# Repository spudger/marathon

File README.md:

# Marathon

A handheld retro gaming console built around a Raspberry Pi Zero 2 W, designed for long battery life through a custom PCB that places every power, audio, and amplifier IC as a bare chip directly on the board.

## Status

- 🔨 **Phase 1, Component identification & research:** mostly complete.
- ✅ **Phase 2, Breadboard prototype:** complete. All subsystems (power, display, audio, buttons) verified end-to-end on 2026-04-03 / 2026-04-04.
- 🔨 **Phase 3, Schematic capture (KiCad):** mostly complete. ERC is clean; a readability pass on the sheet remains.
- 🔨 **Phase 4, PCB layout (KiCad):** in progress. Placement and routing are done, and DRC reports 0 errors. Provisional footprints still need checking against the real parts, and there are no fabrication files yet. Not ready for fabrication.
- 🔨 **Phase 5, Case design:** first concept modeled in CadQuery, with STLs and renders in [`case/`](case/). Not printed yet, and several part sizes are provisional.

See the [Phases](#phases) table below for the full roadmap.

## Design

Marathon integrates its power management (BQ25616 charger, TPS61023 boost, LTC2954 power key controller and MAX17048 fuel gauge), I²S DAC (PCM5102A), and class-D amplifier (PAM8403) as bare ICs on a single custom PCB. The final board is planned for SMT assembly via JLCPCB. The design dedicates internal case volume to a thin, high-capacity LiPo cell, the source of the "Marathon" name.

Design highlights:

- **Bare-chip build.** Every IC is soldered directly to the PCB, not mounted on breakout modules.
- **Safe charging and clean shutdown.** A BQ25616 charges the cell at 0.9 A, only between 0 °C and 45 °C, and runs the device from USB while it charges. A TPS61023 boosts the cell to 5 V. The power key turns the device on with a 1 s hold and shuts Linux down cleanly with a short press; a MAX17048 gauge reports the battery level so the Pi can shut down before the cell runs out.
- **Long-life battery.** Target about 4000 mAh, from a 105060-class cell about 10 mm thick. The board reserves a 67 x 59 mm area on the back, for a cell up to 57 x 65 mm with its protection board (`planning/specs/022-BATTERY-SPACE.md`).
- **Direct I²S audio chain.** Pi → PCM5102A DAC → PAM8403 amplifier → two speakers. A hardware SPDT mute switch holds the amp in shutdown for instant silence, and fixed attenuation keeps full-scale audio under the speakers' 1 W rating at the amp's nominal gain. Fine volume control is handled in RetroPie.
- **Direct GPIO input.** Silicone membrane pads for the D-pad and ABXY, tactile switches for Start, Select, and shoulder buttons. No I²C expander.
- **USB-C with spec-compliant CC resistors.** Works with any USB-C cable, not just A-to-C.
- **Landscape handheld form factor.** A 160 x 75 mm board with the screen in the middle, the D-pad on the left, and the face buttons on the right.

The main board without its case, front and back, rendered from the KiCad layout.

## System Architecture

Power flow and signal flow across the Marathon hardware:

```mermaid
flowchart LR
    USBC[USB-C in]
    BAT[3.7V LiPo<br/>about 4000 mAh]
    CHG[BQ25616<br/>charger + power path]
    BOOST[TPS61023<br/>5V boost]
    KEY[LTC2954<br/>power key]
    GAUGE[MAX17048<br/>fuel gauge]
    V5((5V rail))
    V33((3.3V rail))
    PI[Raspberry Pi<br/>Zero 2 W]
    MUTE{SPDT mute<br/>switch}
    PAM[PAM8403<br/>class-D amp]
    DAC[PCM5102A<br/>I2S DAC]
    LCD[ILI9341<br/>3.2 inch SPI LCD]
    SPK1[Speaker L]
    SPK2[Speaker R]
    DPAD[D-pad<br/>silicone pad]
    ABXY[ABXY<br/>silicone pad]
    TACT[Start / Select<br/>L / R shoulders]

    USBC --> CHG
    BAT <--> CHG
    CHG -->|SYS| BOOST
    BOOST --> V5
    KEY -->|enable| BOOST
    KEY <-->|shutdown request / kill| PI
    BAT --- GAUGE
    GAUGE -->|I2C| PI
    V5 --> PI
    V5 --> PAM
    MUTE -->|shutdown| PAM
    V5 -->|backlight| LCD
    PI --> V33
    V33 --> LCD
    V33 --> DAC
    PI -->|SPI| LCD
    PI -->|I2S| DAC
    DAC -->|analog L/R| PAM
    PAM --> SPK1
    PAM --> SPK2
    DPAD -->|GPIO| PI
    ABXY -->|GPIO| PI
    TACT -->|GPIO| PI
```

## Phases

| Phase | Scope | Status |
|-------|-------|--------|
| 1 | Component identification & research | 🔨 Mostly complete |
| 2 | Breadboard prototype | ✅ Complete (2026-04-03 / 2026-04-04) |
| 3 | Schematic capture (KiCad) | 🔨 Mostly complete |
| 4 | PCB layout (KiCad) | 🔨 In progress |
| 5 | Case design (3D print) | 🔨 First concept |
| 6 | Software & RetroPie tuning | 🔨 Partial (validated during Phase 2) |
| 7 | Fabrication & final assembly (JLCPCB + hand-solder) | ⏳ Planned |

Full phase detail is in [`documentation/PROJECT_PLAN.md`](documentation/PROJECT_PLAN.md).

## Repository Layout

```
marathon/
├── .claude/skills/verify-marathon/       ERC, DRC, BOM and renders of the KiCad project, vs main
├── README.md                             this file
├── LICENSE                               CERN-OHL-P v2
├── bom/                                  bill of materials, sourcing, decision log
├── documentation/
│   ├── PROJECT_PLAN.md                   design overview, architecture, phase roadmap
│   ├── PIN_MAPPING.md                    complete 40-pin GPIO map across all subsystems
│   └── PROTOTYPE_BUILD_GUIDE.md          step-by-step breadboard prototype build guide
├── schematics/                           schematic PDF export (planned)
├── pcb/                                  KiCad 10 project: schematic, layout, libraries, renders
├── case/                                 the 3D-printed case: CadQuery source, STEP, STLs, renders
├── software/                             firmware and OS configuration (Phase 6)
└── tools/render/                         board renders and the stand-in 3D models
```

`software/` is a placeholder for a later phase.

## Build Documentation

- **Breadboard prototype build:** [`documentation/PROTOTYPE_BUILD_GUIDE.md`](documentation/PROTOTYPE_BUILD_GUIDE.md): full walkthrough from USB-C cable harvest through verified I²S audio and joystick input, including all config files and gotchas.
- **Pin mapping:** [`documentation/PIN_MAPPING.md`](documentation/PIN_MAPPING.md): the full 40-pin GPIO table, subsystem breakdowns, and display / audio / button pin assignments.
- **Bill of materials:** [`bom/`](bom/): every component with specs, costs, sourcing, and a running decision log.
- **Project plan:** [`documentation/PROJECT_PLAN.md`](documentation/PROJECT_PLAN.md): architecture overview and the full phase roadmap.

## Hardware Stack

| Subsystem | Component | Notes |
|-----------|-----------|-------|
| Compute | Raspberry Pi Zero 2 W | Mounts on the back of the PCB on standoffs, joined by long-tail header pins |
| Display | ILI9341 3.2" SPI LCD | 18-pin FPC ribbon soldered directly to the PCB |
| Audio DAC | PCM5102A (bare IC) | I²S input, line-level output |
| Audio amp | PAM8403 (bare IC) | Class-D stereo, drives two speakers |
| Power | BQ25616, TPS61023, LTC2954, MAX17048 (bare ICs) | Charging with temperature cutoff, 5 V boost, power key with clean shutdown, battery level |
| Battery | 3.7 V LiPo, about 4000 mAh target | 105060-class cell, about 10 mm thick |
| Input | Silicone membrane pads + tactile switches | Direct GPIO, no expander |
| Case | Custom 3D print | First concept: two shells, 164.2 x 79.2 x 18.5 mm, held by four M2 screws (`case/`) |

## License

Licensed under the [CERN Open Hardware Licence version 2, Permissive (CERN-OHL-P v2)](https://ohwr.org/project/cernohl/wikis/Documents/CERN-OHL-version-2). See [`LICENSE`](LICENSE).

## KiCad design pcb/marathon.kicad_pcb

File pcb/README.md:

# PCB

KiCad 10 project for the Marathon main board. Open `marathon.kicad_pro`. The schematic lives here with the layout because KiCad keeps a project's files in one folder.

**Status:** Phase 4, in progress. **Not ready for fabrication.**

- 160 x 75 mm, 2 layers.
- Placed: every part. The Raspberry Pi mounts on the back, inside the outline and clear of the battery area.
- Routed: every net, with ground pours on both layers that fill the rounded corners.
- Four plated M2 case holes (H1 to H4), tied to GND, 5 mm in from each edge.
- 13 test pads (TP1 to TP13) on the back, labeled with their net names, outside the Pi, the microSD card's overhang, the battery and the antenna areas.
- The `PI_ANTENNA_KEEPOUT` rule area keeps tracks, vias, pads and pours off both layers under the Pi Zero 2 W's antenna, plus 5 mm, or 4.2 mm on the left where the D-pad's right contact (SW13) sits. The antenna sits on the Pi's edge opposite the GPIO header, between the mini-HDMI and USB data ports.
- U2 (PCM5102A) and U3 (PAM8403) use their library footprints flipped to the back, so their pin order matches the parts (fixed 2026-11-06). Their capacitors moved with them, and each bypass capacitor sits at the pin the schematic names.
- Footprints named `PROVISIONAL` still need checking against the real parts. The Alps switch footprints follow Alps' published land patterns.
- `marathon.kicad_dru` allows 0.12 mm clearance inside the U5 (SOT-563) and U6 (TSOT-23-8) courtyards, whose stock land patterns put pads 0.15 mm apart.
- The BQ25616 uses a project copy of KiCad's RTW footprint with four 0.3 mm vias in the exposed pad, the board's minimum drill.
- The stackup sets a black solder mask and an ENIG finish on the 1.0 mm board.
- `Marathon.3dshapes/` holds stand-in 3D models for the project footprints, and BT1 is a board-only stand-in for the battery. `tools/render/` builds them and the renders.

## Renders

Flat views: [`renders/top.png`](renders/top.png) and [`renders/bottom.png`](renders/bottom.png). To rebuild them, see [`../tools/render/README.md`](../tools/render/README.md).

## Checks

| Check | Result |
|-------|--------|
| ERC | 0 violations |
| DRC | 0 errors, 0 warnings |
| Unrouted connections | 0 |
| Schematic / PCB parity | 0 issues |

To re-run them from the repo root:

```bash
kicad-cli sch erc pcb/marathon.kicad_sch
kicad-cli pcb drc --refill-zones --schematic-parity pcb/marathon.kicad_pcb
```

## Planned

- A `fab/` folder with Gerbers, drill files, BOM, and pick-and-place files for JLCPCB.

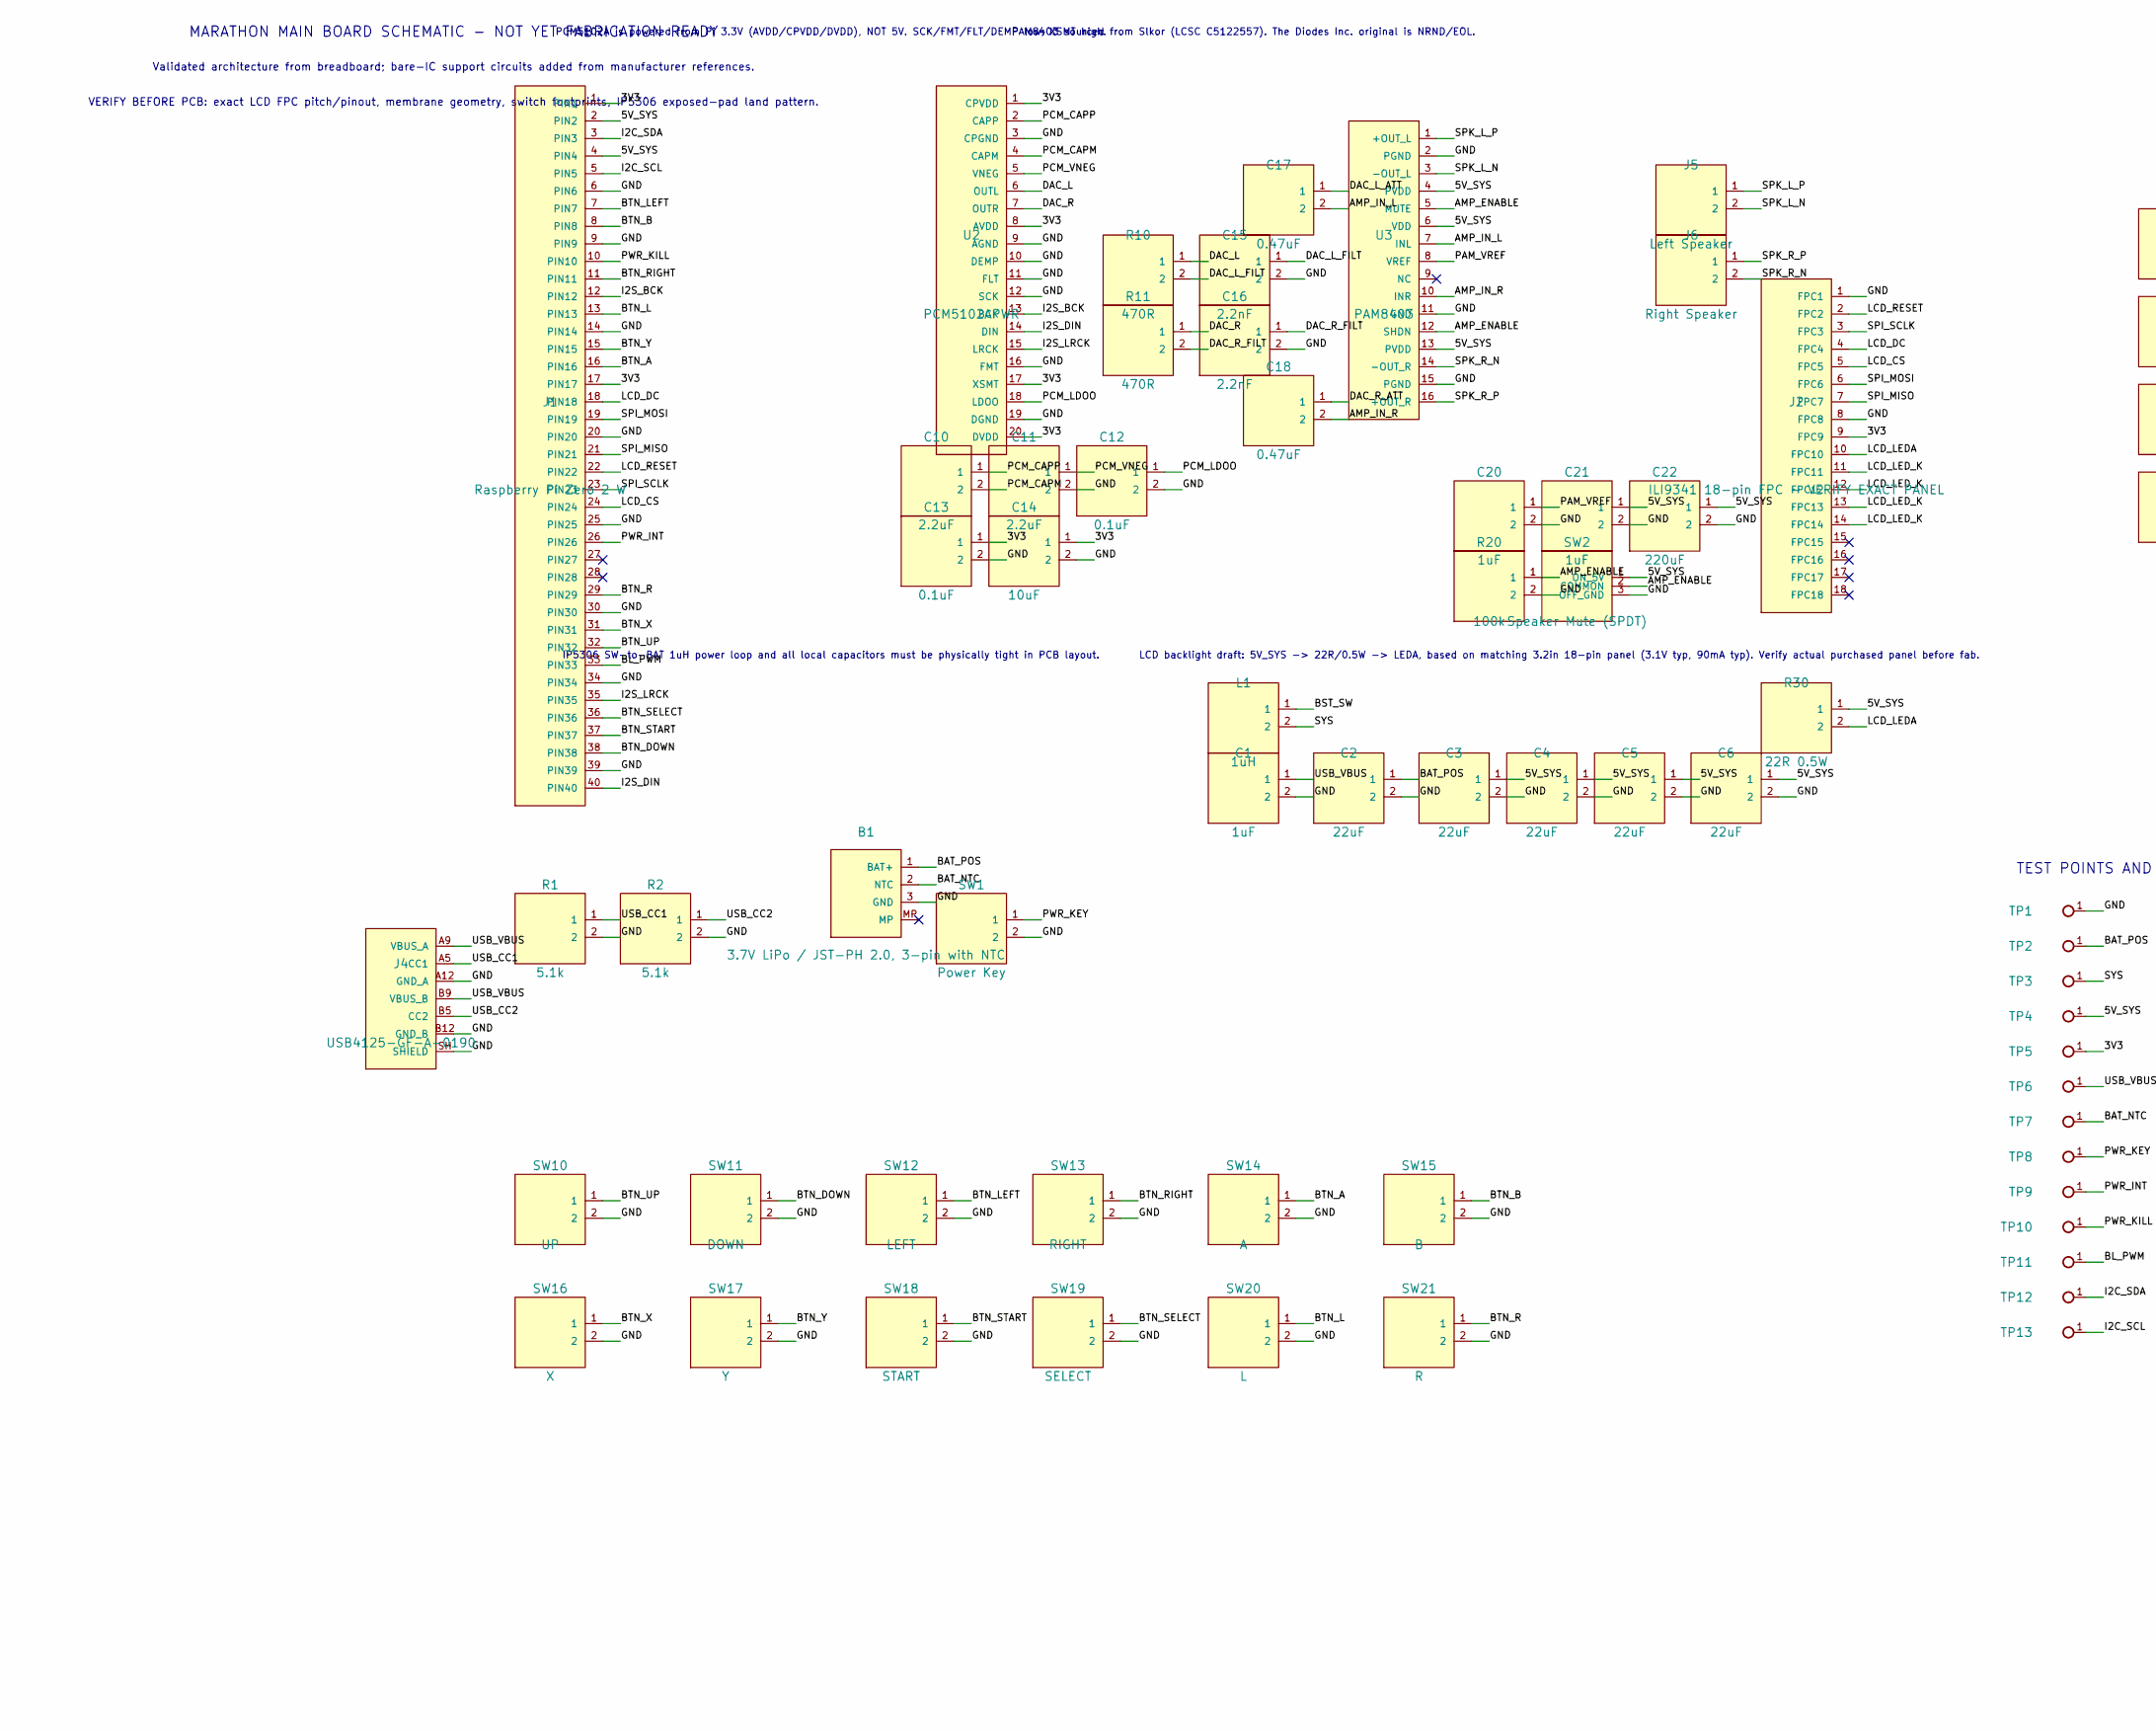
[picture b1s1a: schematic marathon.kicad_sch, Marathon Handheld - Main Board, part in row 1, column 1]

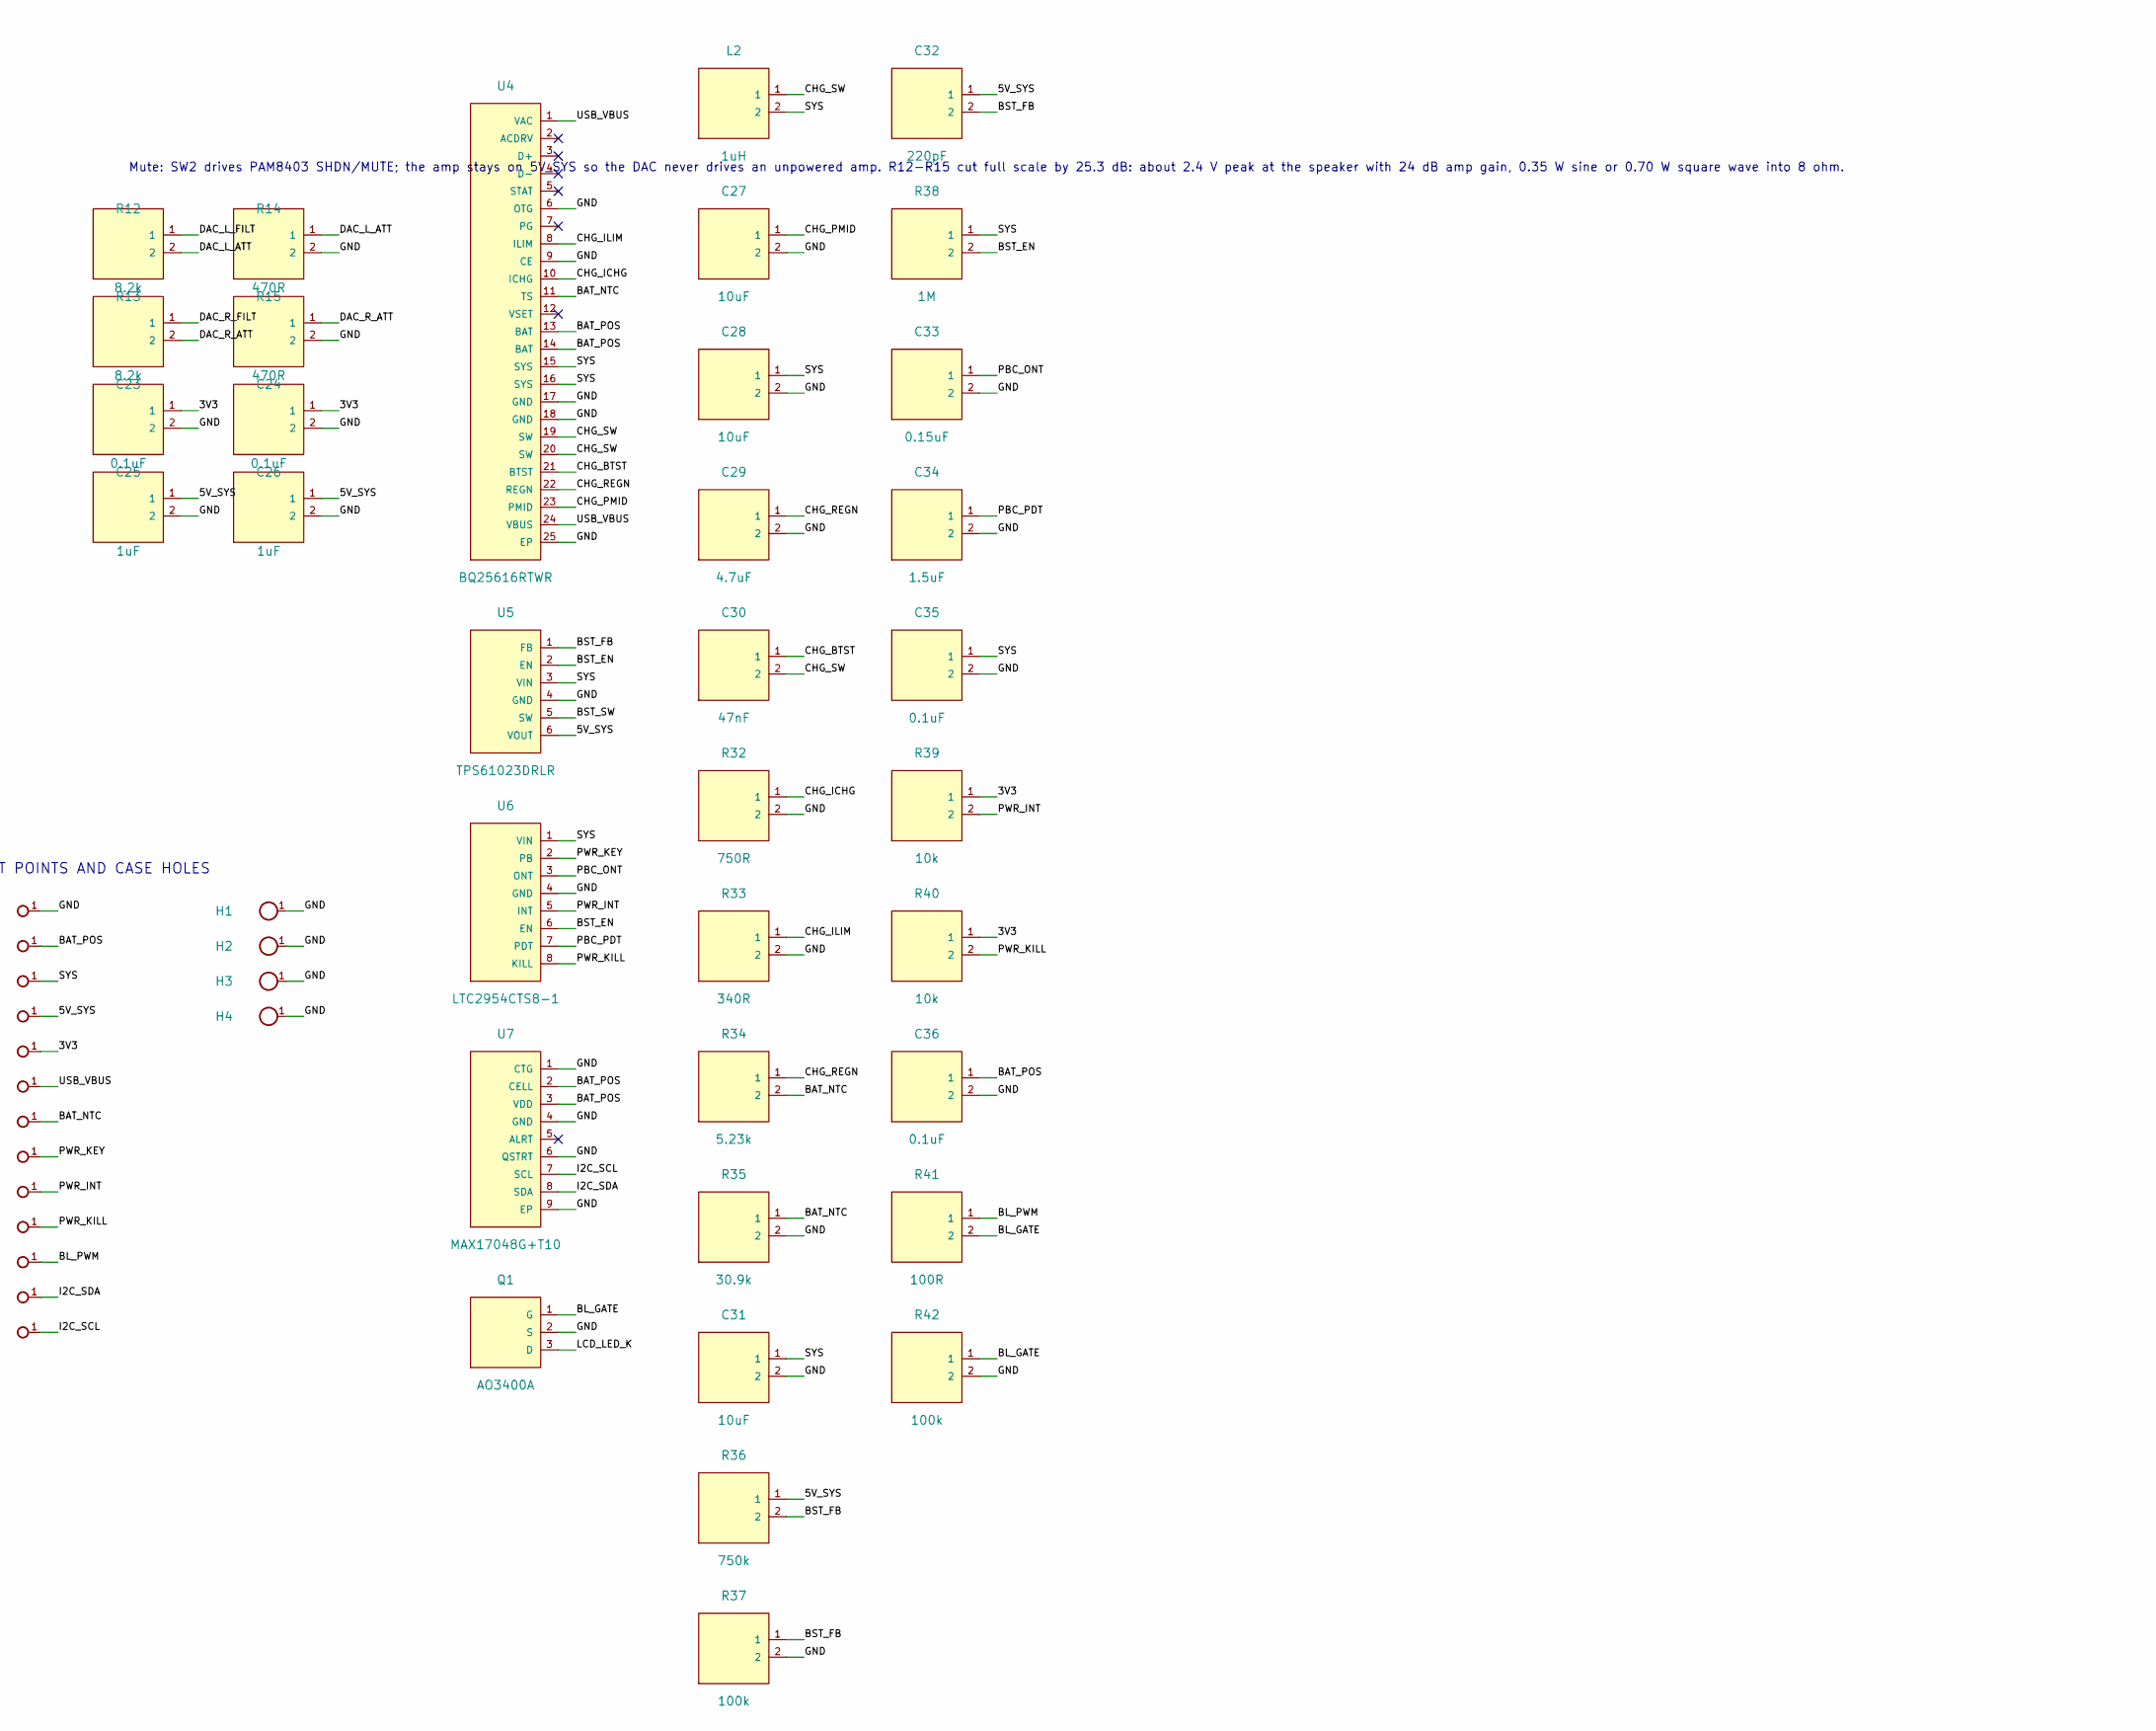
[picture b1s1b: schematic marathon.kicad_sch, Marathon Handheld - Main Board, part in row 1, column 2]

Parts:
B1: 3.7V LiPo / JST-PH 2.0, 3-pin with NTC; JST_PH_S3B-PH-SM4-TB_1x03-1MP_P2.00mm_Horizontal
C1, C21: 1uF; C_0805_2012Metric_Pad1.18x1.45mm_HandSolder
C2, C3, C4, C5, C6: 22uF; C_0805_2012Metric_Pad1.18x1.45mm_HandSolder
C10, C11: 2.2uF; C_0402_1005Metric
C12, C13, C23, C24, C35, C36: 0.1uF; C_0402_1005Metric
C14, C27: 10uF; C_0603_1608Metric
C15, C16: 2.2nF; C_0603_1608Metric
C17, C18: 0.47uF; C_0603_1608Metric
C20, C25, C26: 1uF; C_0603_1608Metric
C22: 220uF; CP_EIA-7343-31_Kemet-D; MPN Panasonic 10TPE220ML; LCSC C147767
C28, C31: 10uF; C_0805_2012Metric_Pad1.18x1.45mm_HandSolder
C29: 4.7uF; C_0603_1608Metric
C30: 47nF; C_0402_1005Metric
C32: 220pF; C_0402_1005Metric
C33: 0.15uF; C_0603_1608Metric; Tolerance 10%
C34: 1.5uF; C_0603_1608Metric; Tolerance 10%
H1, H2, H3, H4: MountingHole_M2; MountingHole_2.2mm_M2_Pad_Via
J1: Raspberry Pi Zero 2 W; Raspberry_Pi_Zero_2W_DirectStack_THT
J2: ILI9341 18-pin FPC - VERIFY EXACT PANEL; LCD_FPC18_P0.8_DirectSolder_PROVISIONAL
J4: USB4125-GF-A-0190; USB_C_Receptacle_GCT_USB4125-xx-x-0190_6P_TopMnt_Horizontal; MPN USB4125-GF-A-0190; LCSC C5246813
J5: Left Speaker; Speaker_WirePads_2P_P5.0
J6: Right Speaker; Speaker_WirePads_2P_P5.0
L1: 1uH; L_Coilcraft_XAL4020-XXX
L2: 1uH; L_1008_2520Metric; MPN TDK TFM252012ALMA1R0MTAA; LCSC C404802
Q1: AO3400A; SOT-23; MPN AO3400A; LCSC C20917
R1, R2: 5.1k; R_0603_1608Metric_Pad0.98x0.95mm_HandSolder
R10, R11, R14, R15: 470R; R_0603_1608Metric_Pad0.98x0.95mm_HandSolder
R12, R13: 8.2k; R_0603_1608Metric_Pad0.98x0.95mm_HandSolder
R20, R42: 100k; R_0603_1608Metric_Pad0.98x0.95mm_HandSolder
R30: 22R 0.5W; R_1206_3216Metric_Pad1.30x1.75mm_HandSolder
R32: 750R; R_0603_1608Metric_Pad0.98x0.95mm_HandSolder; Tolerance 1%
R33: 340R; R_0603_1608Metric_Pad0.98x0.95mm_HandSolder; Tolerance 1%
R34: 5.23k; R_0603_1608Metric_Pad0.98x0.95mm_HandSolder; Tolerance 1%
R35: 30.9k; R_0603_1608Metric_Pad0.98x0.95mm_HandSolder; Tolerance 1%
R36: 750k; R_0603_1608Metric_Pad0.98x0.95mm_HandSolder; Tolerance 1%
R37: 100k; R_0603_1608Metric_Pad0.98x0.95mm_HandSolder; Tolerance 1%
R38: 1M; R_0603_1608Metric_Pad0.98x0.95mm_HandSolder
R39, R40: 10k; R_0603_1608Metric_Pad0.98x0.95mm_HandSolder
R41: 100R; R_0603_1608Metric_Pad0.98x0.95mm_HandSolder
SW1: Power Key; SW_Alps_SKTHACE010_PROVISIONAL; MPN SKTHACE010
SW2: Speaker Mute (SPDT); SS12F15_G5_THT
SW10: UP; Conductive_Pad_5mm_GameBoyStyle
SW11: DOWN; Conductive_Pad_5mm_GameBoyStyle
SW12: LEFT; Conductive_Pad_5mm_GameBoyStyle
SW13: RIGHT; Conductive_Pad_5mm_GameBoyStyle
SW14: A; Conductive_Pad_5mm_GameBoyStyle
SW15: B; Conductive_Pad_5mm_GameBoyStyle
SW16: X; Conductive_Pad_5mm_GameBoyStyle
SW17: Y; Conductive_Pad_5mm_GameBoyStyle
SW18: START; SW_Alps_SKTHACE010_PROVISIONAL; MPN SKTHACE010
SW19: SELECT; SW_Alps_SKTHACE010_PROVISIONAL; MPN SKTHACE010
SW20: L; SW_Alps_SKSCLDE010_PROVISIONAL; MPN SKSCLDE010
SW21: R; SW_Alps_SKSCLDE010_PROVISIONAL; MPN SKSCLDE010
TP1: GND; TestPoint_Pad_D1.0mm
TP2: BAT_POS; TestPoint_Pad_D1.0mm
TP3: SYS; TestPoint_Pad_D1.0mm
TP4: 5V_SYS; TestPoint_Pad_D1.0mm
TP5: 3V3; TestPoint_Pad_D1.0mm
TP6: USB_VBUS; TestPoint_Pad_D1.0mm
TP7: BAT_NTC; TestPoint_Pad_D1.0mm
TP8: PWR_KEY; TestPoint_Pad_D1.0mm
TP9: PWR_INT; TestPoint_Pad_D1.0mm
TP10: PWR_KILL; TestPoint_Pad_D1.0mm
TP11: BL_PWM; TestPoint_Pad_D1.0mm
TP12: I2C_SDA; TestPoint_Pad_D1.0mm
TP13: I2C_SCL; TestPoint_Pad_D1.0mm
U2: PCM5102APWR; TSSOP-20_4.4x6.5mm_P0.65mm; MPN PCM5102APWR; LCSC C107671
U3: PAM8403; SOIC-16_3.9x9.9mm_P1.27mm; MPN PAM8403 (Slkor); LCSC C5122557
U4: BQ25616RTWR; Texas_RTW_WQFN-24-1EP_4x4mm_P0.5mm_EP2.7x2.7mm_Vias0.3; MPN BQ25616RTWR; LCSC C2866447
U5: TPS61023DRLR; SOT-563; MPN TPS61023DRLR; LCSC C919459
U6: LTC2954CTS8-1; TSOT-23-8; MPN LTC2954CTS8-1#TRPBF; LCSC C683782
U7: MAX17048G+T10; TDFN-8-1EP_2x2mm_P0.5mm_EP0.8x1.2mm; MPN MAX17048G+T10; LCSC C2682616

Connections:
/3V3: C13.1, C14.1, C23.1, C24.1, J1.1 (PIN1), J1.17 (PIN17), J2.9 (FPC9), R39.1, R40.1, TP5.1, U2.1 (CPVDD), U2.8 (AVDD), U2.17 (XSMT), U2.20 (DVDD)
/5V_SYS: C3.1, C4.1, C5.1, C6.1, C21.1, C22.1, C25.1, C26.1, C32.1, J1.2 (PIN2), J1.4 (PIN4), R30.1, R36.1, SW2.1 (ON_5V), TP4.1, U3.4 (PVDD), U3.6 (VDD), U3.13 (PVDD), U5.6 (VOUT)
/AMP_ENABLE: R20.1, SW2.2 (COMMON), U3.5 (MUTE), U3.12 (SHDN)
/AMP_IN_L: C17.2, U3.7 (INL)
/AMP_IN_R: C18.2, U3.10 (INR)
/BAT_NTC: B1.2 (NTC), R34.2, R35.1, TP7.1, U4.11 (TS)
/BAT_POS: B1.1 (BAT+), C2.1, C36.1, TP2.1, U4.13 (BAT), U4.14 (BAT), U7.2 (CELL), U7.3 (VDD)
/BL_GATE: Q1.1 (G), R41.2, R42.1
/BL_PWM: J1.33 (PIN33), R41.1, TP11.1
/BST_EN: R38.2, U5.2 (EN), U6.6 (EN)
/BST_FB: C32.2, R36.2, R37.1, U5.1 (FB)
/BST_SW: L1.1, U5.5 (SW)
/BTN_A: J1.16 (PIN16), SW14.1
/BTN_B: J1.8 (PIN8), SW15.1
/BTN_DOWN: J1.38 (PIN38), SW11.1
/BTN_L: J1.13 (PIN13), SW20.1
/BTN_LEFT: J1.7 (PIN7), SW12.1
/BTN_R: J1.29 (PIN29), SW21.1
/BTN_RIGHT: J1.11 (PIN11), SW13.1
/BTN_SELECT: J1.36 (PIN36), SW19.1
/BTN_START: J1.37 (PIN37), SW18.1
/BTN_UP: J1.32 (PIN32), SW10.1
/BTN_X: J1.31 (PIN31), SW16.1
/BTN_Y: J1.15 (PIN15), SW17.1
/CHG_BTST: C30.1, U4.21 (BTST)
/CHG_ICHG: R32.1, U4.10 (ICHG)
/CHG_ILIM: R33.1, U4.8 (ILIM)
/CHG_PMID: C27.1, U4.23 (PMID)
/CHG_REGN: C29.1, R34.1, U4.22 (REGN)
/CHG_SW: C30.2, L2.1, U4.19 (SW), U4.20 (SW)
/DAC_L: R10.1, U2.6 (OUTL)
/DAC_L_ATT: C17.1, R12.2, R14.1
/DAC_L_FILT: C15.1, R10.2, R12.1
/DAC_R: R11.1, U2.7 (OUTR)
/DAC_R_ATT: C18.1, R13.2, R15.1
/DAC_R_FILT: C16.1, R11.2, R13.1
/GND: B1.3 (GND), C1.2, C2.2, C3.2, C4.2, C5.2, C6.2, C11.2, C12.2, C13.2, C14.2, C15.2, C16.2, C20.2, C21.2, C22.2, C23.2, C24.2, C25.2, C26.2, C27.2, C28.2, C29.2, C31.2, C33.2, C34.2, C35.2, C36.2, H1.1, H2.1, H3.1, H4.1, J1.6 (PIN6), J1.9 (PIN9), J1.14 (PIN14), J1.20 (PIN20), J1.25 (PIN25), J1.30 (PIN30), J1.34 (PIN34), J1.39 (PIN39), J2.1 (FPC1), J2.8 (FPC8), J4.A12 (GND_A), J4.B12 (GND_B), J4.SH (SHIELD), Q1.2 (S), R1.2, R2.2, R14.2, R15.2, R20.2, R32.2, R33.2, R35.2, R37.2, R42.2, SW1.2, SW2.3 (OFF_GND), SW10.2, SW11.2, SW12.2, SW13.2, SW14.2, SW15.2, SW16.2, SW17.2, SW18.2, SW19.2, SW20.2, SW21.2, TP1.1, U2.3 (CPGND), U2.9 (AGND), U2.10 (DEMP), U2.11 (FLT), U2.12 (SCK), U2.16 (FMT), U2.19 (DGND), U3.2 (PGND), U3.11 (GND), U3.15 (PGND), U4.6 (OTG), U4.9 (CE), U4.17 (GND), U4.18 (GND), U4.25 (EP), U5.4 (GND), U6.4 (GND), U7.1 (CTG), U7.4 (GND), U7.6 (QSTRT), U7.9 (EP)
/I2C_SCL: J1.5 (PIN5), TP13.1, U7.7 (SCL)
/I2C_SDA: J1.3 (PIN3), TP12.1, U7.8 (SDA)
/I2S_BCK: J1.12 (PIN12), U2.13 (BCK)
/I2S_DIN: J1.40 (PIN40), U2.14 (DIN)
/I2S_LRCK: J1.35 (PIN35), U2.15 (LRCK)
/LCD_CS: J1.24 (PIN24), J2.5 (FPC5)
/LCD_DC: J1.18 (PIN18), J2.4 (FPC4)
/LCD_LEDA: J2.10 (FPC10), R30.2
/LCD_LED_K: J2.11 (FPC11), J2.12 (FPC12), J2.13 (FPC13), J2.14 (FPC14), Q1.3 (D)
/LCD_RESET: J1.22 (PIN22), J2.2 (FPC2)
/PAM_VREF: C20.1, U3.8 (VREF)
/PBC_ONT: C33.1, U6.3 (ONT)
/PBC_PDT: C34.1, U6.7 (PDT)
/PCM_CAPM: C10.2, U2.4 (CAPM)
/PCM_CAPP: C10.1, U2.2 (CAPP)
/PCM_LDOO: C12.1, U2.18 (LDOO)
/PCM_VNEG: C11.1, U2.5 (VNEG)
/PWR_INT: J1.26 (PIN26), R39.2, TP9.1, U6.5 (INT)
/PWR_KEY: SW1.1, TP8.1, U6.2 (PB)
/PWR_KILL: J1.10 (PIN10), R40.2, TP10.1, U6.8 (KILL)
/SPI_MISO: J1.21 (PIN21), J2.7 (FPC7)
/SPI_MOSI: J1.19 (PIN19), J2.6 (FPC6)
/SPI_SCLK: J1.23 (PIN23), J2.3 (FPC3)
/SPK_L_N: J5.2, U3.3 (-OUT_L)
/SPK_L_P: J5.1, U3.1 (+OUT_L)
/SPK_R_N: J6.2, U3.14 (-OUT_R)
/SPK_R_P: J6.1, U3.16 (+OUT_R)
/SYS: C28.1, C31.1, C35.1, L1.2, L2.2, R38.1, TP3.1, U4.15 (SYS), U4.16 (SYS), U5.3 (VIN), U6.1 (VIN)
/USB_CC1: J4.A5 (CC1), R1.1
/USB_CC2: J4.B5 (CC2), R2.1
/USB_VBUS: C1.1, J4.A9 (VBUS_A), J4.B9 (VBUS_B), TP6.1, U4.1 (VAC), U4.24 (VBUS)

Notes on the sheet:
MARATHON MAIN BOARD SCHEMATIC - NOT YET FABRICATION READY
Validated architecture from breadboard; bare-IC support circuits added from manufacturer references.
VERIFY BEFORE PCB: exact LCD FPC pitch/pinout, membrane geometry, switch footprints, IP5306 exposed-pad land pattern.
PCM5102A is powered from Pi 3.3V (AVDD/CPVDD/DVDD), NOT 5V. SCK/FMT/FLT/DEMP low; XSMT high.
PAM8403 sourced from Slkor (LCSC C5122557). The Diodes Inc. original is NRND/EOL.
IP5306 SW-to-BAT 1uH power loop and all local capacitors must be physically tight in PCB layout.
LCD backlight draft: 5V_SYS -> 22R/0.5W -> LEDA, based on matching 3.2in 18-pin panel (3.1V typ, 90mA typ). Verify actual purchased panel before fab.
Mute: SW2 drives PAM8403 SHDN/MUTE; the amp stays on 5V_SYS so the DAC never drives an unpowered amp. R12-R15 cut full scale by 25.3 dB: about 2.4 V peak at the speaker with 24 dB amp gain, 0.35 W sine or 0.70 W square wave into 8 ohm.
TEST POINTS AND CASE HOLES

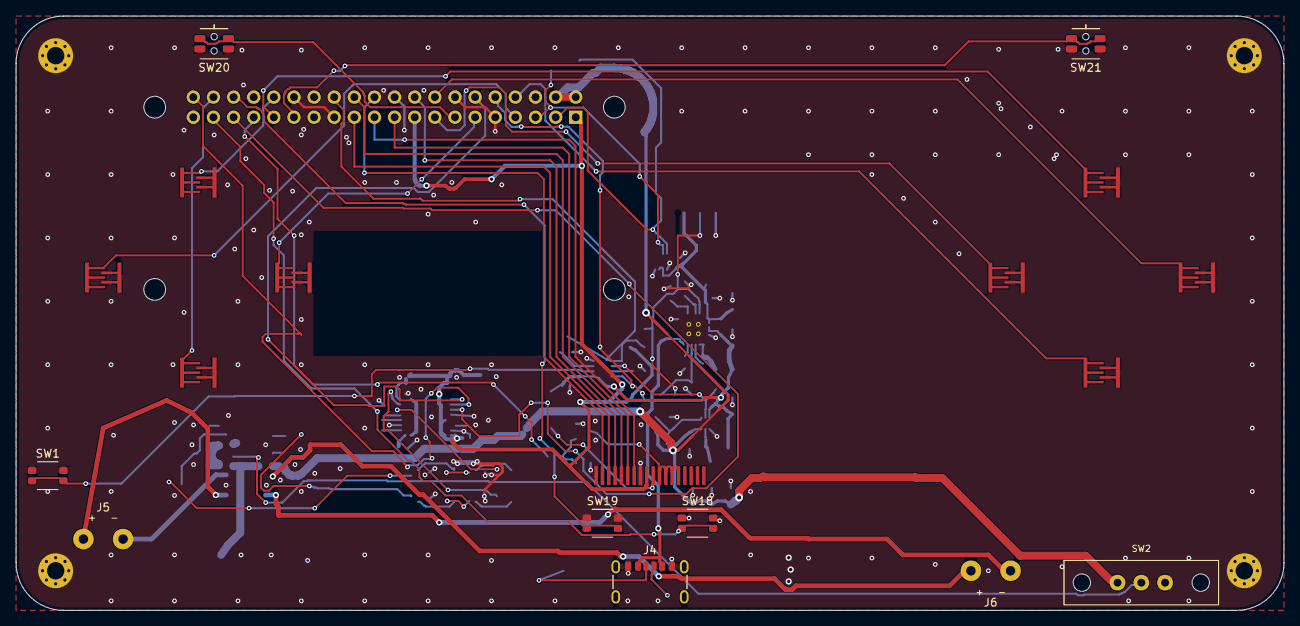
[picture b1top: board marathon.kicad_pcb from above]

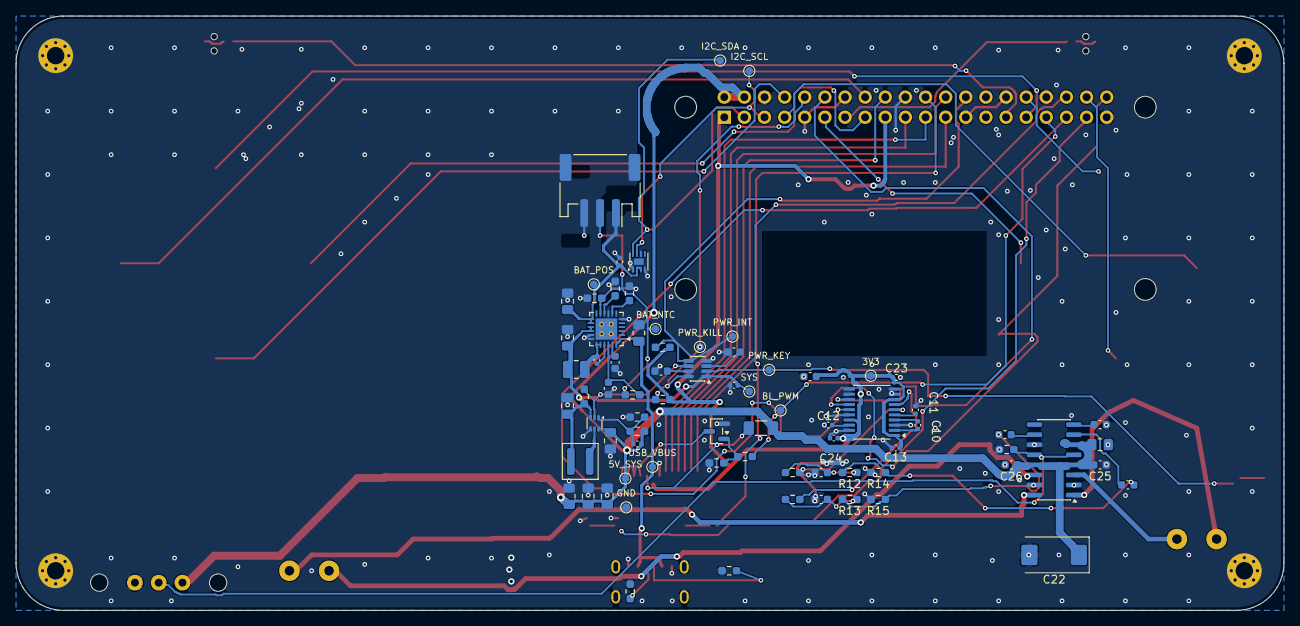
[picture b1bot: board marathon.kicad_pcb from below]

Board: 2 copper layers, 160.0 x 75.0 mm, 100 parts (78 on the bottom side), 68 nets.

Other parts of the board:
BT1: Battery_LiPo_105063_StandIn
